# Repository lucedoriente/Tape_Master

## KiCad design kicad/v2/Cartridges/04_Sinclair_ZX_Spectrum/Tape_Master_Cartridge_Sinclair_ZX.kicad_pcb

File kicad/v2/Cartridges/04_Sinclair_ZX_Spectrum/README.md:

# Tape Master v2 — Cartuccia #04: Sinclair ZX Spectrum / ZX81 / Timex Sinclair

Modulo di interfaccia cassetta hardware conforme allo standard **Tape Master v2 (Tape/Cassette Master Exerciser & Signal Digitizer)** progettato da **Alessio Iodice**.

---

## 1. Modelli e Piattaforme Supportate
La cartuccia supporta la totalità della famiglia Sinclair a 8 bit e i relativi cloni compatibili:
- **Sinclair ZX80 / ZX81** (jack standard 3.5 mm MIC/EAR)
- **Sinclair ZX Spectrum 16K / 48K** ("Rubber Keys" e "Plus")
- **Sinclair ZX Spectrum 128K** ("Toastrack")
- **Sinclair ZX Spectrum +2** (Grigio con Datacorder integrato e prese ausiliarie)
- **Sinclair ZX Spectrum +2A / +2B / +3** (Nero - Amstrad design)
- **Timex Sinclair 1000 / 1500 / 2068**
- **Cloni internazionali**: Microdigital TK85, TK90X, TK95 (Brasile), Didaktik Gama / M (Cecoslovacchia), Pentagon / Scorpion (URSS).

---

## 2. Architettura Elettronica e Circuiti di Segnale

### A. Uscita Verso il Computer (`SPECTRUM_EAR` / Jack J2)
- **Livello Segnale e Attenuazione**: Il microcontrollore Tape Master genera segnali digitali a 3.3V/5V (`TAPE_EMU_OUT`). La porta EAR dello Spectrum accetta ampiezze nominali da $0.7\text{ V}$ a $1.5\text{ V}_\text{pp}$.
- **Buffer di Pilotaggio**: Buffer invertitore open-collector ad alta velocità **74HCT06** (`U2`), configurato a doppio stadio con resistenze di pull-up da $4.7\text{ k}\Omega$ (`R8`, `R9`) a +5V.
- **Partitore e Disaccoppiamento AC**: Partitore resistivo simmetrico $1\text{ k}\Omega / 1\text{ k}\Omega$ (`R6`, `R7`) per ridurre il segnale a circa $1.25\text{ V}_\text{pp}$, seguito da condensatore elettrolitico/tantalio SMD da $4.7\ \mu\text{F}$ (`C4`) per il disaccoppiamento della componente continua.

### B. Ingresso dal Computer (`SPECTRUM_MIC` / Jack J3)
- **Doppio Percorso di Acquisizione**:
  1. **Percorso Digitale MCU (`TAPE_REC_IN`)**: Partitore resistivo $2.2\text{ k}\Omega / 3.3\text{ k}\Omega$ (`R1`, `R2`) con stadio di clamp a diodi Schottky ultraveloci **BAT54S** (`D1`) verso GND e +3.3V, per una cattura a squadratura perfetta senza jitter.
  2. **Percorso Analogico Digitizer (`AUDIO_RAW_L`)**: Disaccoppiamento in frequenza tramite condensatore da $4.7\ \mu\text{F}$ (`C5`) diretto al convertitore analogico ADC e alla barra VU-meter a 10 segmenti frontale.

### C. Controllo Motore Remoto (`SPECTRUM_REM_A` / Header J4)
- Interruttore a stato solido basato su MOSFET a canale N **2N7002** (`Q1`) pilotato dalla linea `MOTOR_SENSE` con resistenza di pull-up da $10\text{ k}\Omega$ (`R3`), in grado di emulare il relè del telecomando registratore per registratori esterni compatibili.

### D. Protezione ESD e Auto-Riconoscimento Smart Plug&Play
- **Protezione TVS**: Array di diodi ad altissima velocità **USBLC6-2SC6** (`D2`) su tutte le linee esterne esposte (`EAR`, `MIC`, `REM_A`).
- **EEPROM I2C 24C02 (`U1`)**: Indirizzo hardware `0x54` (`A2=1`, `A1=0`, `A0=0`), contenente il descrittore binario Plug&Play con identificativo cartuccia `#04`, mapping piedini e parametri di temporizzazione ULA.

---

## 3. Connettività Esterna e Banco di Collaudo

### Connettori Audio Jack 3.5 mm TRS (CUI SJ1-3533NG)
- **`J2` (`EAR` / Riproduzione verso Spectrum)**:
  - `Tip (T)`: Segnale `SPECTRUM_EAR`
  - `Ring (R)`: Connesso a Tip per piena compatibilità con cavetti sia mono sia stereo
  - `Sleeve (S)`: Massa (`GND`)
- **`J3` (`MIC` / Registrazione dallo Spectrum)**:
  - `Tip (T)`: Segnale `SPECTRUM_MIC`
  - `Ring (R)`: Connesso a Tip per compatibilità con cavetti mono e stereo
  - `Sleeve (S)`: Massa (`GND`)

### Pin Header Banco di Prova (`J4` - Maschio 1x06 passo 2.54 mm)
| Pin | Segnale Serigrafato | Funzione Elettrica |
| :---: | :---: | :--- |
| **1** | `GND` | Riferimento di massa 0V |
| **2** | `+5V` | Alimentazione secondaria ausiliaria |
| **3** | `EAR` | Linea audio riproduzione diretta / oscilloscopio |
| **4** | `MIC` | Linea audio acquisizione grezza / analizzatore |
| **5** | `REM` | Linea controllo motore registratore |
| **6** | `GND` | Riferimento di massa 0V |

---

## 4. Specifiche Meccaniche e PCB
- **Dimensioni Esterne**: $74.00\text{ mm} \times 55.00\text{ mm}$ con profilo Edge.Cuts standard.
- **Intagli Laterali di Ritenuta**: Due aperture $6.00\text{ mm} \times 8.00\text{ mm}$ per le leve di aggancio rapido (latch) del connettore Mainboard.
- **Connettore Bus**: $2 \times 20$ contatti femmina a 90° (`J1`), perfettamente complanare alla Mainboard.
- **Finitura**: Piani di massa rame continui su Top (`F.Cu`) e Bottom (`B.Cu`), serigrafia con dicitura d'autore `© 2026 by Alessio Iodice`.

---

## 5. Validazione KiCad 9.0 e File di Fabbricazione
- **Controllo Regole Elettriche (ERC)**: `0 errori / 0 avvisi`
- **Controllo Regole di Design (DRC)**: `0 violazioni / 0 net non connesse / 0 discrepanze netlist-PCB`
- **File Inclusi**:
  - `Tape_Master_Cartridge_Sinclair_ZX.kicad_sch` (Schema elettrico)
  - `Tape_Master_Cartridge_Sinclair_ZX.kicad_pcb` (Layout sbrogliato e verificato)
  - `Tape_Master_Cartridge_Sinclair_ZX.pdf` (Tavola vettoriale dello schema)
  - `Tape_Master_Cartridge_Sinclair_ZX.step` (Modello 3D solido MCAD con tutti i componenti integrati)
  - `Tape_Master_Cartridge_Sinclair_ZX_Top.pdf` / `Bottom.pdf` / `Top.svg` (Plottaggi serigrafia e rame)
  - `gerbers/` (26 file standard RS-274X e forature Excellon pronti per JLCPCB/PCBWay).

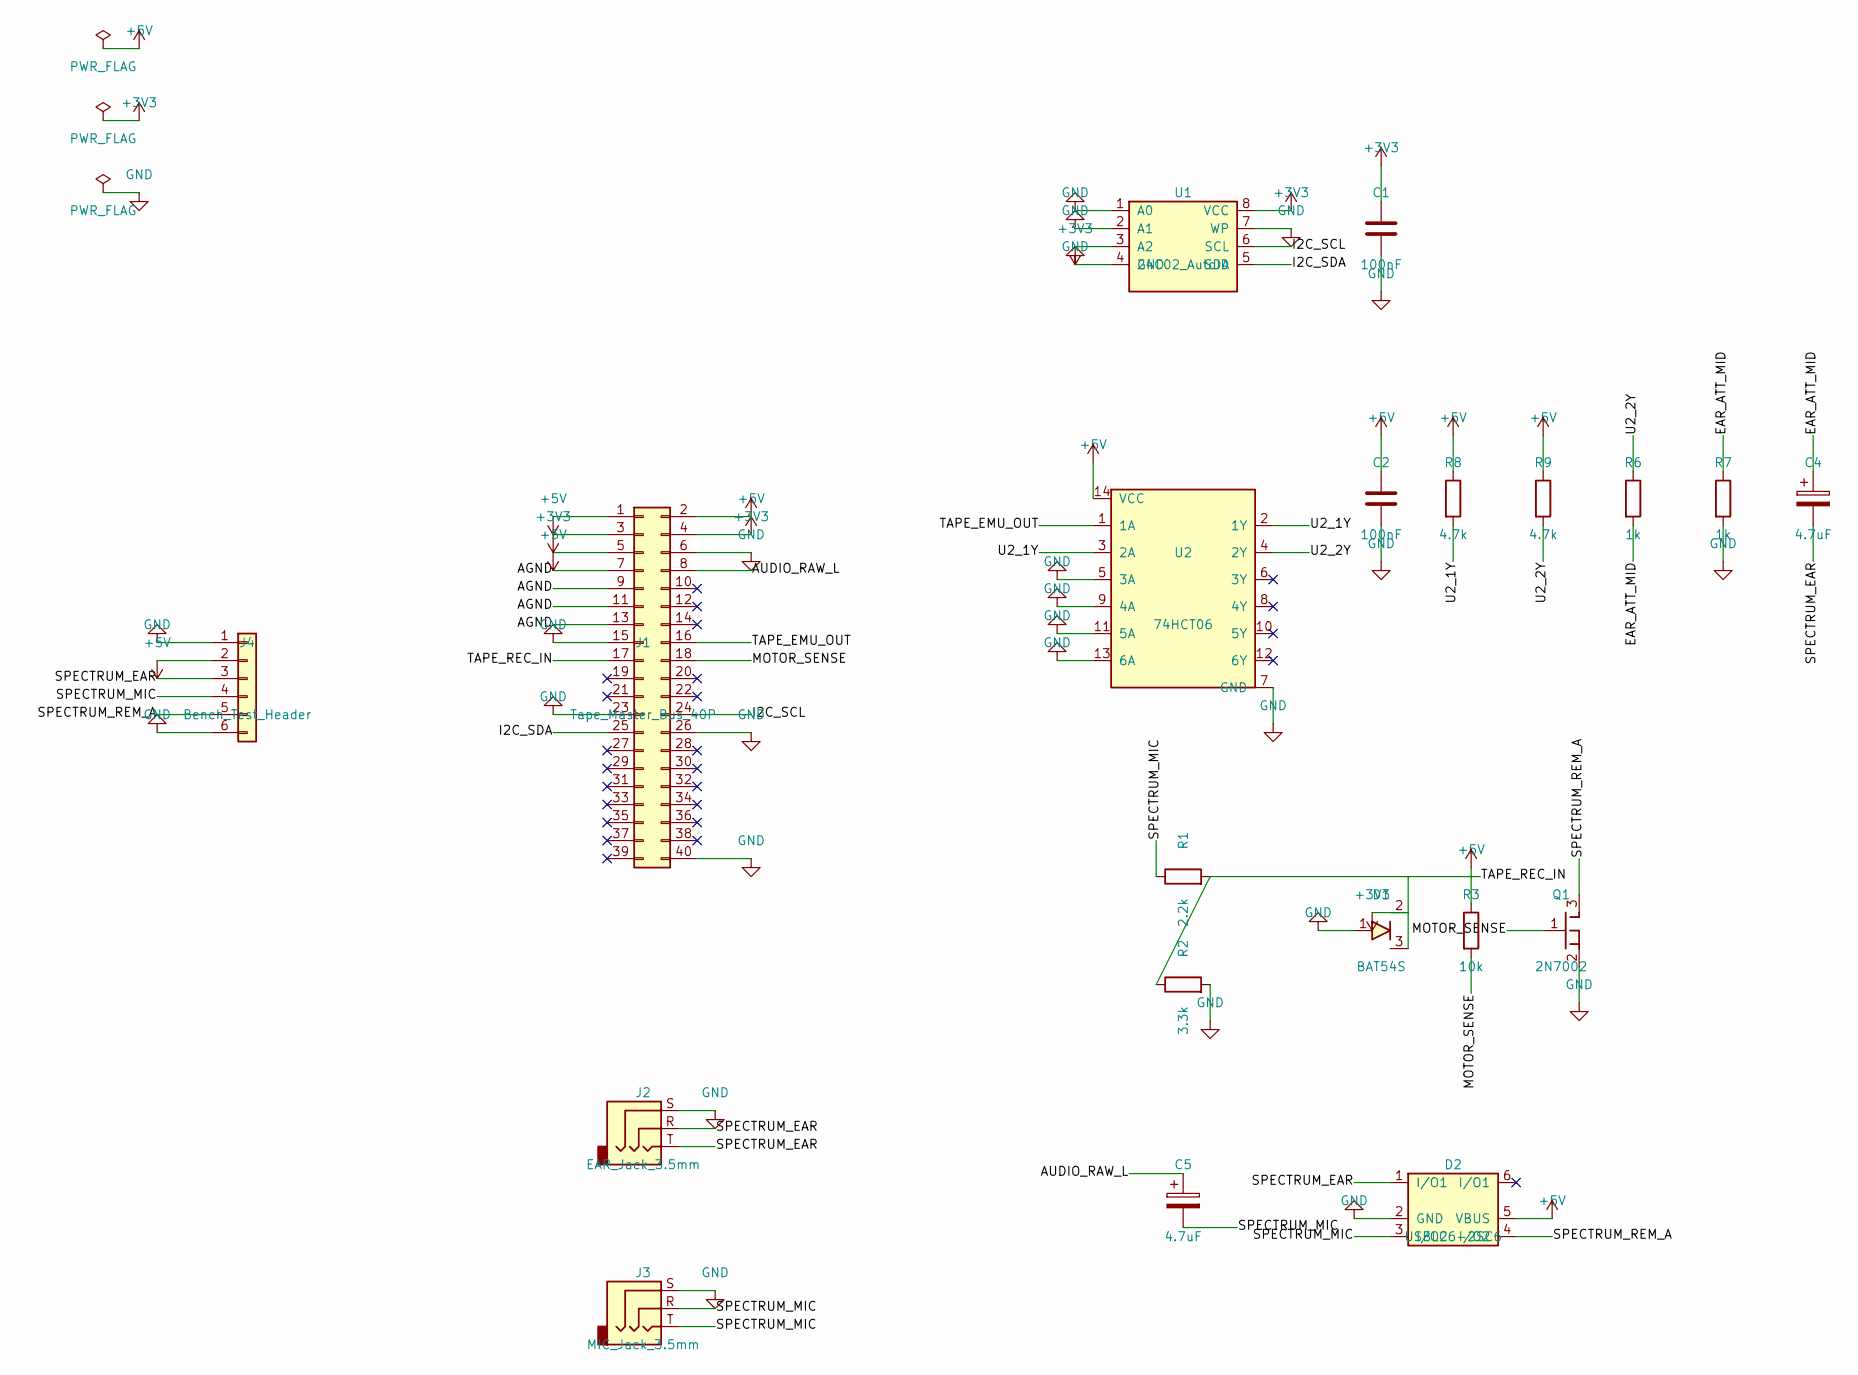
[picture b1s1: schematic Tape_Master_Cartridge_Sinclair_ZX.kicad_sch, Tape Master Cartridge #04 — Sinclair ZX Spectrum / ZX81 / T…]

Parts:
C1, C2: 100nF; C_0805_2012Metric
C4, C5: 4.7uF; CP_Elec_5x5.4
D1: BAT54S; SOT-23
D2: USBLC6-2SC6; SOT-23-6
J1: Tape_Master_Bus_40P; PinSocket_2x20_P2.54mm_Horizontal_Cartridge
J2: EAR_Jack_3.5mm; Jack_3.5mm_CUI_SJ1-3525N_Horizontal
J3: MIC_Jack_3.5mm; Jack_3.5mm_CUI_SJ1-3525N_Horizontal
J4: Bench_Test_Header; PinHeader_1x06_P2.54mm_Vertical
Q1: 2N7002; SOT-23
R1: 2.2k; R_0805_2012Metric
R2: 3.3k; R_0805_2012Metric
R3: 10k; R_0805_2012Metric
R6, R7: 1k; R_0805_2012Metric
R8, R9: 4.7k; R_0805_2012Metric
U1: 24C02_AutoID; SOIC-8_3.9x4.9mm_P1.27mm
U2: 74HCT06; SOIC-14_3.9x8.7mm_P1.27mm

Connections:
+3V3: C1.1, D1.2 (C2), J1.3, J1.4, U1.3 (A2), U1.8 (VCC)
+5V: C2.1, D2.5 (VBUS), J1.1, J1.2, J1.5, J4.2, R3.1, R8.1, R9.1, U2.14 (VCC)
/AGND: J1.7, J1.9, J1.11, J1.13
/AUDIO_RAW_L: C5.1, J1.8
/EAR_ATT_MID: C4.1, R6.2, R7.1
/I2C_SCL: J1.24, U1.6 (SCL)
/I2C_SDA: J1.25, U1.5 (SDA)
/MOTOR_SENSE: J1.18, Q1.1 (G), R3.2
/SPECTRUM_EAR: C4.2, D2.1 (I/O1), J2.R, J2.T, J4.3
/SPECTRUM_MIC: C5.2, D2.3 (I/O2), J3.R, J3.T, J4.4, R1.1
/SPECTRUM_REM_A: D2.4 (I/O2), J4.5, Q1.3 (D)
/TAPE_EMU_OUT: J1.16, U2.1 (1A)
/TAPE_REC_IN: D1.3 (C1A2), J1.17, R1.2, R2.1
/U2_1Y: R8.2, U2.2 (1Y), U2.3 (2A)
/U2_2Y: R6.1, R9.2, U2.4 (2Y)
GND: C1.2, C2.2, D1.1 (A1), D2.2 (GND), J1.6, J1.15, J1.23, J1.26, J1.40, J2.S, J3.S, J4.1, J4.6, Q1.2 (S), R2.2, R7.2, U1.1 (A0), U1.2 (A1), U1.4 (GND), U1.7 (WP), U2.5 (3A), U2.7 (GND), U2.9 (4A), U2.11 (5A), U2.13 (6A)

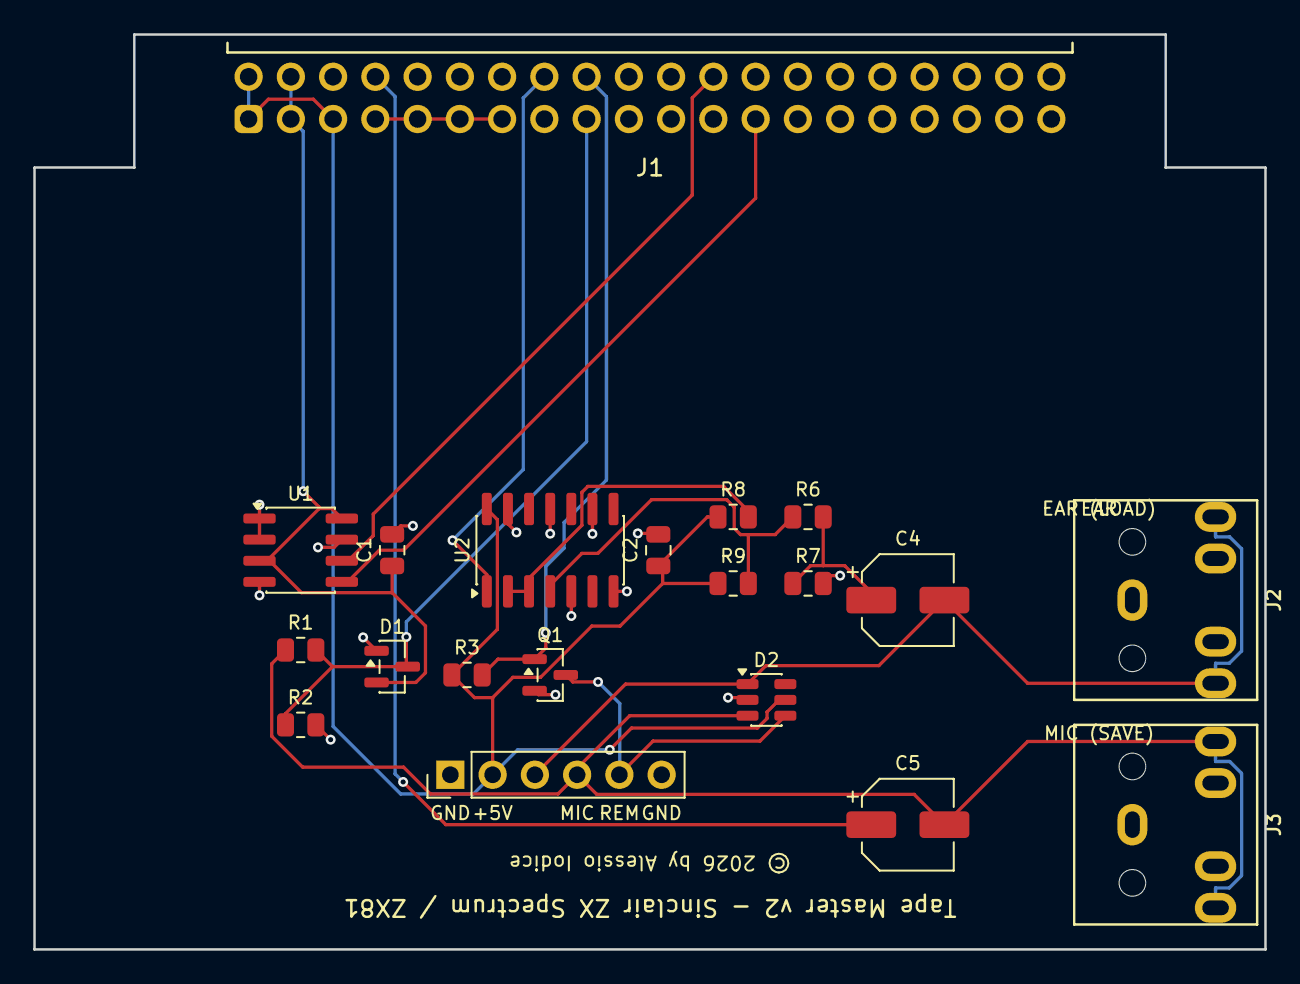
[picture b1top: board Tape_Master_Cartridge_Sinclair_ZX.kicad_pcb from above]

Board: 2 copper layers, 74.0 x 55.0 mm, 20 parts (0 on the bottom side), 16 nets.

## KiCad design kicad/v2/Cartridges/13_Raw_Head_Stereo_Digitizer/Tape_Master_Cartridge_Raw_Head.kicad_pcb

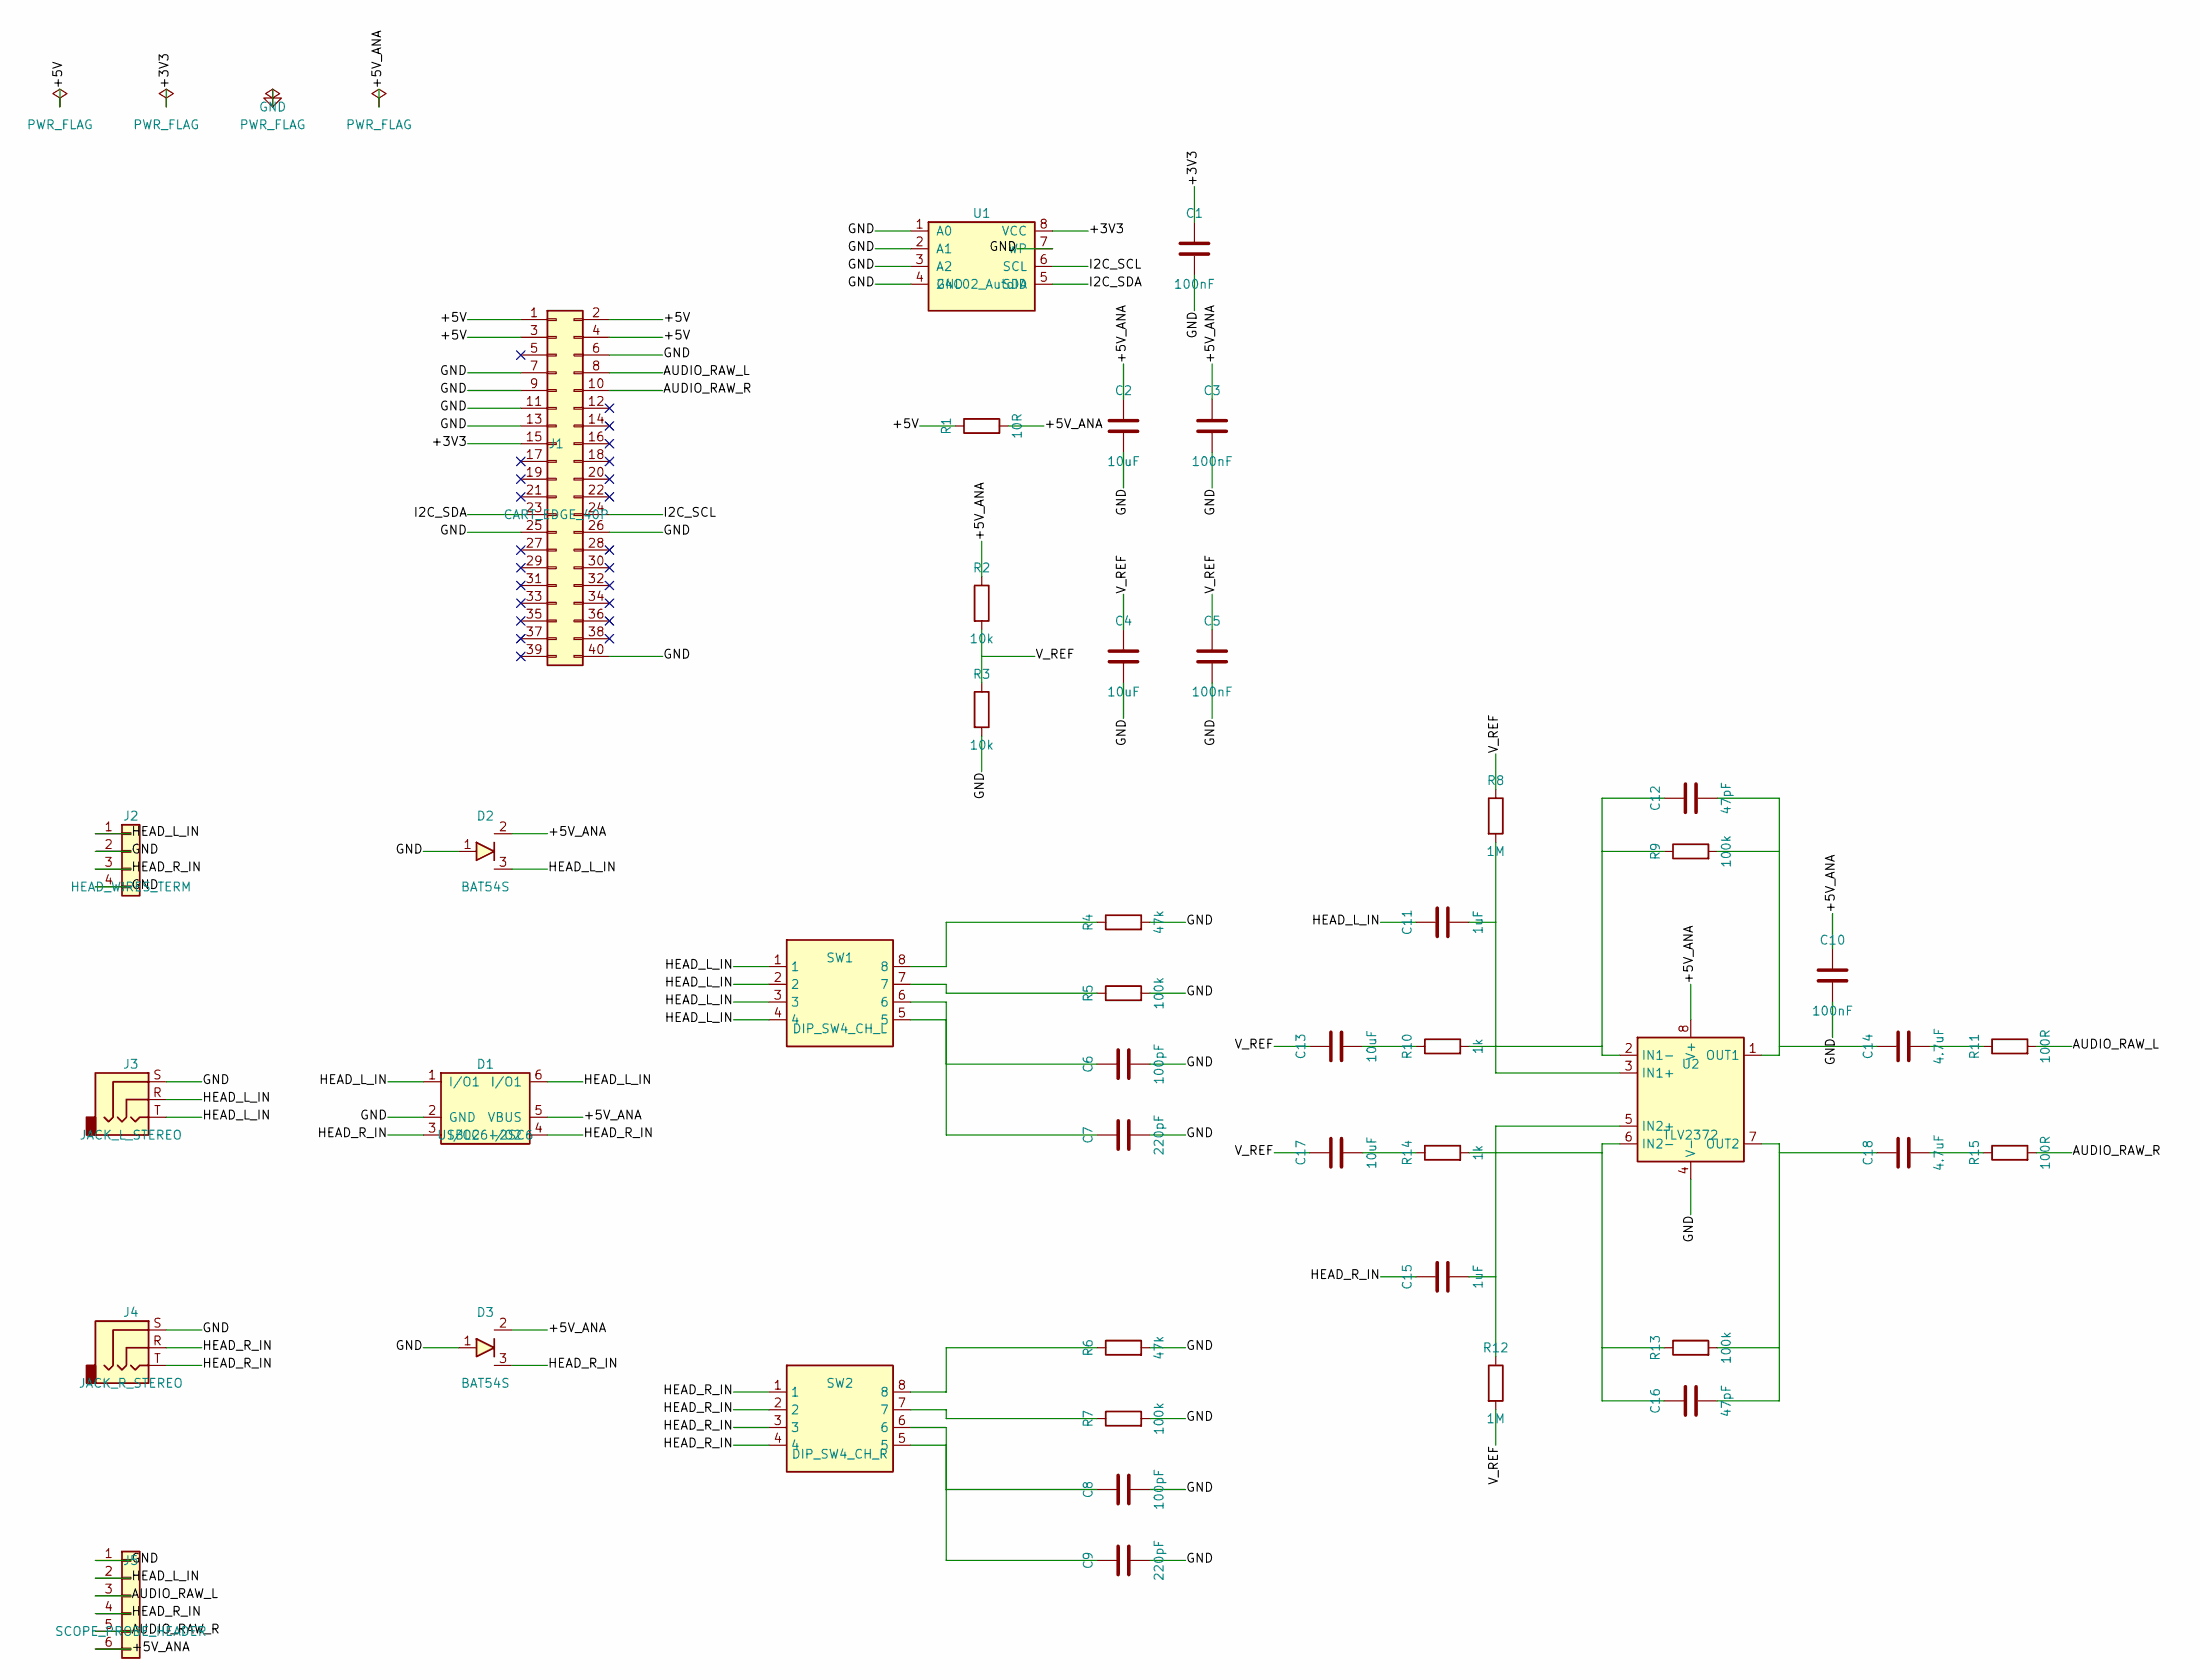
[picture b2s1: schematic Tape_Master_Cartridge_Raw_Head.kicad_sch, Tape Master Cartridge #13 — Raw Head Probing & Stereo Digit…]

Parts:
C1, C3, C5, C10: 100nF; C_0805_2012Metric
C2, C4, C13, C17: 10uF; C_0805_2012Metric
C6, C8: 100pF; C_0805_2012Metric
C7, C9: 220pF; C_0805_2012Metric
C11, C15: 1uF; C_0805_2012Metric
C12, C16: 47pF; C_0805_2012Metric
C14, C18: 4.7uF; C_0805_2012Metric
D1: USBLC6-2SC6; SOT-23-6
D2, D3: BAT54S; SOT-23
J1: CART_EDGE_40P; PinSocket_2x20_P2.54mm_Horizontal_Cartridge
J2: HEAD_WIRES_TERM; TerminalBlock_Phoenix_MPT-0,5-4-2.54_1x04_P2.54mm_Horizontal
J3: JACK_L_STEREO; Jack_3.5mm_CUI_SJ-3523-SMT_Horizontal
J4: JACK_R_STEREO; Jack_3.5mm_CUI_SJ-3523-SMT_Horizontal
J5: SCOPE_PROBE_HEADER; PinHeader_1x06_P2.54mm_Vertical
R1: 10R; R_0805_2012Metric
R2, R3: 10k; R_0805_2012Metric
R4, R6: 47k; R_0805_2012Metric
R5, R7, R9, R13: 100k; R_0805_2012Metric
R8, R12: 1M; R_0805_2012Metric
R10, R14: 1k; R_0805_2012Metric
R11, R15: 100R; R_0805_2012Metric
SW1: DIP_SW4_CH_L; SW_DIP_SPSTx04_Slide_6.7x11.72mm_W8.61mm_P2.54mm_LowProfile
SW2: DIP_SW4_CH_R; SW_DIP_SPSTx04_Slide_6.7x11.72mm_W8.61mm_P2.54mm_LowProfile
U1: 24C02_AutoID; SOIC-8_3.9x4.9mm_P1.27mm
U2: TLV2372; SOIC-8_3.9x4.9mm_P1.27mm

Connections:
/+3V3: C1.1, J1.15, U1.8 (VCC)
/+5V: J1.1, J1.2, J1.3, J1.4, R1.1
/+5V_ANA: C2.1, C3.1, C10.1, D1.5 (VBUS), D2.2 (C2), D3.2 (C2), J5.6, R1.2, R2.1, U2.8 (V+)
/AUDIO_RAW_L: J1.8, J5.3, R11.2
/AUDIO_RAW_R: J1.10, J5.5, R15.2
/HEAD_L_IN: C11.1, D1.1 (I/O1), D1.6 (I/O1), D2.3 (C1A2), J2.1, J3.R, J3.T, J5.2, SW1.1, SW1.2, SW1.3, SW1.4
/HEAD_R_IN: C15.1, D1.3 (I/O2), D1.4 (I/O2), D3.3 (C1A2), J2.3, J4.R, J4.T, J5.4, SW2.1, SW2.2, SW2.3, SW2.4
/I2C_SCL: J1.24, U1.6 (SCL)
/I2C_SDA: J1.23, U1.5 (SDA)
/V_REF: C4.1, C5.1, C13.1, C17.1, R2.2, R3.1, R8.1, R12.2
GND: C1.2, C2.2, C3.2, C4.2, C5.2, C6.2, C7.2, C8.2, C9.2, C10.2, D1.2 (GND), D2.1 (A1), D3.1 (A1), J1.6, J1.7, J1.9, J1.11, J1.13, J1.25, J1.26, J1.40, J2.2, J2.4, J3.S, J4.S, J5.1, R3.2, R4.2, R5.2, R6.2, R7.2, U1.1 (A0), U1.2 (A1), U1.3 (A2), U1.4 (GND), U1.7 (WP), U2.4 (V-)
unnamed: C6.1, SW1.6
unnamed: C7.1, SW1.5
unnamed: C8.1, SW2.6
unnamed: C9.1, SW2.5
unnamed: C13.2, R10.1
unnamed: C14.2, R11.1
unnamed: C17.2, R14.1
unnamed: C18.2, R15.1
unnamed: R4.1, SW1.8
unnamed: R5.1, SW1.7
unnamed: R6.1, SW2.8
unnamed: R7.1, SW2.7
unnamed: C11.2, R8.2, U2.3 (IN1+)
unnamed: C12.1, R9.1, R10.2, U2.2 (IN1-)
unnamed: C15.2, R12.1, U2.5 (IN2+)
unnamed: C16.1, R13.1, R14.2, U2.6 (IN2-)
unnamed: C12.2, C14.1, R9.2, U2.1 (OUT1)
unnamed: C16.2, C18.1, R13.2, U2.7 (OUT2)

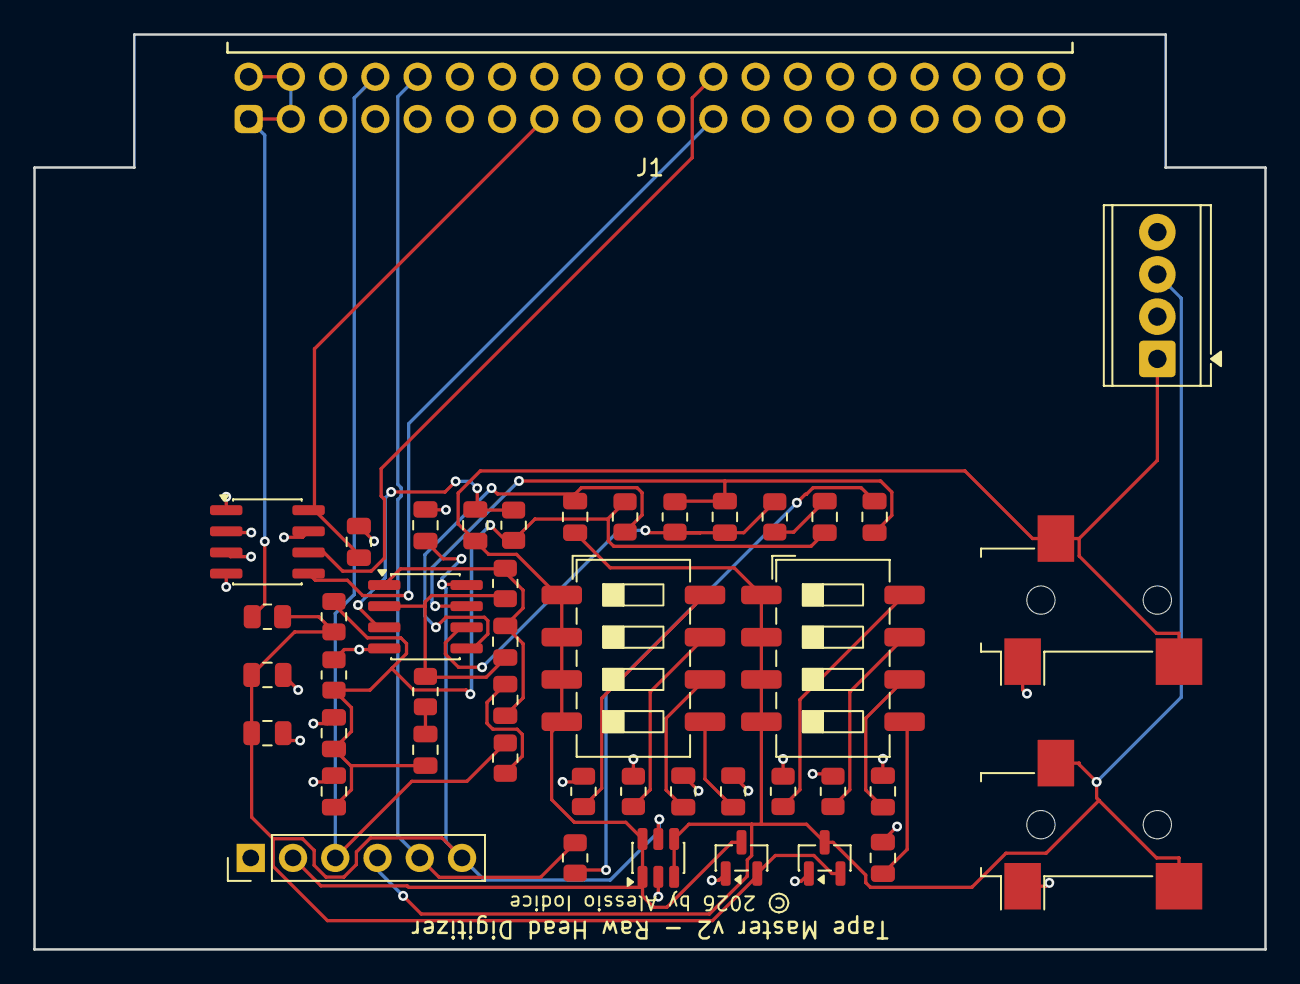
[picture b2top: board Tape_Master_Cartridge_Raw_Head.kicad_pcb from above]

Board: 2 copper layers, 74.0 x 55.0 mm, 45 parts (0 on the bottom side), 29 nets.

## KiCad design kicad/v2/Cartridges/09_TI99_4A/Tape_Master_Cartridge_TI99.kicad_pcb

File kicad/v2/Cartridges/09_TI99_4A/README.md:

# Tape Master v2 — Cartuccia 09: Texas Instruments TI-99/4A Tape Interface

| Proprietà | Dettaglio / Valore |
| :--- | :--- |
| **Progetto** | Tape Master Exerciser & Signal Digitizer v2 |
| **Modulo** | Cartuccia Espansione #09 — Texas Instruments TI-99/4A (`09_TI99_4A`) |
| **Piattaforme Compatibili** | Texas Instruments TI-99/4 e TI-99/4A (microprocessore a 16 bit TMS9900 @ 3.0 MHz) |
| **Periferiche Supportate** | Registratore a nastro dedicato TI Program Recorder PHP2700, registratori audio standard tramite cavo PHA2000 o cavo seriale maschio/femmina DE-9 dritto |
| **Autore & Hardware Designer** | Alessio Iodice (`alessio67@gmail.com`) |
| **Data di Rilascio** | 2026-11-06 |
| **Revisione** | 2.0 (KiCad 9.0 Nativo) |
| **Licenza** | CC BY-NC-SA 4.0 |
| **Stato Validazione KiCad 9** | **0 Violazioni ERC / 0 Violazioni DRC / 0 Net Non Connesse / 0 Parity Issues** |

---

## 1. Descrizione Architetturale

La **Cartuccia 09: Texas Instruments TI-99/4A** interfaccia il sistema **Tape Master v2** alla porta a nastro a 9 poli posta sul retro della console TI-99/4 e TI-99/4A, adottando il connettore standard **D-Sub 9-pin Femmina (DE-9 Socket)** a montaggio su circuito stampato ([DSUB-9_Socket_Horizontal_P2.77x2.84mm_EdgePinOffset9.40mm](file:///C:/Users/aless/OneDrive/temp/Manutenzione/Kicad_Project/Tape_Master/kicad/v2/Cartridges/09_TI99_4A/Tape_Master_Cartridge_TI99.kicad_pcb)).

L'architettura cassetta del TI-99/4A è unica nel panorama degli home computer degli anni '80:
- È controllata direttamente dal chip **TMS9901 PSI** tramite registri **CRU (Communications Register Unit)**;
- Integra **fotoaccoppiatori e stadi di isolamento ottico** interni alla console;
- Supporta nativamente **due registratori simultanei**: **Cassette 1 (CS1)** dedicato alla lettura, e **Cassette 2 (CS2)** per lettura e scrittura;
- Utilizza modulazione audio FSK a 1200 baud nominali ($1379\text{ Hz}$ per il bit `1` / Mark, $689\text{ Hz}$ per il bit `0` / Space).

### Caratteristiche Elettriche Chiave
1. **Canale Riproduzione Dati (TAPE_IN - Pin 8 DE-9)**:
   - Ingresso audio FSK del computer TI-99/4A (comune per la lettura da CS1 o CS2, associato a CRU Bit 27).
   - Pilotaggio tramite buffer open-collector ad alta velocità **74HCT06** (`U2`) configurato a doppio stadio logico con resistori di pull-up da $4.7\text{ k}\Omega$ (`R7`, `R8`) a `+5V`.
   - Rete passiva di disaccoppiamento AC e calibrazione dinamica: resistore serie $1\text{ k}\Omega$ (`R9`), condensatore di disaccoppiamento da $4.7\ \mu\text{F}$ (`C3`) e resistore di carico shunt da $10\text{ k}\Omega$ (`R10`) verso massa, garantendo un'onda audio calibrata e pulita per il comparatore operazionale interno della console.
2. **Canale Registrazione Dati (CS2_OUT - Pin 3 DE-9)**:
   - Uscita audio FSK dal computer TI-99/4A durante le operazioni di salvataggio (`SAVE "CS2"` o `OLD "CS2"`, CRU Bit 25).
   - Traslazione rapida di livello logico verso i 3.3V tramite partitore resistivo ($R_1 = 2.2\text{ k}\Omega$, $R_2 = 3.3\text{ k}\Omega$) protetto da clamp a doppio diodo Schottky ultra-veloce **BAT54S** (`D1`) verso `+3.3V` e `GND`, collegato alla linea `TAPE_REC_IN` dell'RP2040.
   - Derivazione audio analogica AC con condensatore di blocco DC da $4.7\ \mu\text{F}$ (`C4`), filtro RC passa-basso anti-aliasing ($R_{11} = 1\text{ k}\Omega$, $C_5 = 10\text{ nF}$) e shunt da $10\text{ k}\Omega$ (`R12`) collegata al canale ADC `AUDIO_RAW_L` per il pilotaggio dinamico del display OLED e del VU-meter a 10 segmenti del front panel.
3. **Gestione Indipendente del Doppio Motore (CS1 e CS2)**:
   - **Registratore 1 (`TI_CS1_MOTOR_P`, Pin 1 DE-9 - CRU Bit 22)**:
     - Resistore di pull-up da $10\text{ k}\Omega$ (`R3`) a `+5V`.
     - Partitore $2.2\text{ k}\Omega / 3.3\text{ k}\Omega$ (`R4`, `R5`) con clamp Schottky **BAT54S** (`D2`) attestato sulla linea `MOTOR_SENSE` del bus universale. Quando il computer attiva il motore di CS1, il contatto dell'optoisolatore interno alla console chiude Pin 1 a massa, portando `MOTOR_SENSE` a 0V (attivo basso).
     - N-MOSFET di commutazione **2N7002** (`Q1`) pilotato dalla linea `MOTOR_CTRL` (con resistore serie di gate `R13` da $100\ \Omega$ e pull-down `R14` da $100\text{ k}\Omega$) per consentire al Tape Master di azionare direttamente il motore di un registratore esterno a banco.
   - **Registratore 2 (`TI_CS2_MOTOR_P`, Pin 6 DE-9 - CRU Bit 23)**:
     - Resistore di pull-up da $10\text{ k}\Omega$ (`R15`) a `+5V`.
     - Partitore $2.2\text{ k}\Omega / 3.3\text{ k}\Omega$ (`R16`, `R17`) con clamp Schottky **BAT54S** (`D4`) attestato sulla linea ausiliaria configurabile **`AUX_GPIO1`** (Pin 21 del bus a 40 pin), consentendo al firmware del Tape Master di monitorare separatamente e in tempo reale lo stato del secondo registratore.
4. **Campionamento Audio Gate (`TI_AUDIO_GATE` - Pin 4 DE-9 - CRU Bit 24)**:
   - Partitore resistivo ($R_{18} = 2.2\text{ k}\Omega$, $R_{19} = 3.3\text{ k}\Omega$) con clamp Schottky **BAT54S** (`D5`) collegato alla linea **`AUX_GPIO2`** (Pin 22 del bus a 40 pin) per rilevare l'abilitazione hardware del segnale audio operata dalla console.
5. **Protezione ESD / Transitori**:
   - Due array integrati a diodi TVS ultra-rapidi a bassissima capacità **USBLC6-2SC6** (`U3` e `U4`, package SOT-23-6L) proteggono le linee esterne del connettore DE-9 da scariche elettrostatiche fino a $\pm 15\text{ kV}$.
6. **Smart Plug & Play (Auto-ID Cartridge)**:
   - EEPROM I2C seriale **24C02** (`U1`) all'indirizzo `0x50` con descrittore hardware binario univoco TI-99/4A.
   - Pin 26 del bus principale `CART_DETECT_N` vincolato permanentemente a massa per rilevamento hardware istantaneo all'inserimento.

---

## 2. Centralizzazione Diagnostica sul Front Panel (Daughterboard)

Come prescritto dalle regole ufficiali di progetto `tape-master-rules.md`, tutti i LED diagnostici sono centralizzati sul pannello frontale (`Tape_Master_UI_Panel`), evitando duplicati non visibili a banco sulla cartuccia.

I 5 LED diagnostici standardizzati sul pannello operatore riflettono il funzionamento della cartuccia TI-99/4A:

| Riferimento UI | Colore | Serigrafia Standard | Segnale Mappato per TI-99/4A | Funzione Operativa |
| :---: | :---: | :---: | :--- | :--- |
| **D2** | Verde | **`PLAY`** | `TI_TAPE_IN` (Pin 8 DE-9) | Trasmissione dati FSK verso la console TI-99 (emulazione nastro / riproduzione file WAV o dump) |
| **D3** | Rosso | **`REC`** | `TI_CS2_OUT` (Pin 3 DE-9) | Ricezione dati FSK dalla console TI-99/4A verso il Tape Master (salvataggio dump da `SAVE "CS2"`) |
| **D4** | Giallo | **`MOTOR`** | `TI_CS1_MOTOR_P` (Pin 1 DE-9) | Relè motore CS1 chiuso dalla console o forzatura motore esterna attiva |
| **D5** | Blu | **`SIGNAL`** | Rilevamento portante FSK | Rilevamento toni FSK a $1379\text{ Hz}$ (Mark) o $689\text{ Hz}$ (Space) |
| **D6** | Verde | **`PWR`** | Alimentazione Tape Master | Alimentazione principale di sistema attiva (+5V / +3.3V) e MCU operativo |
| **D10..D19** | 8V/1G/1R | **`AZIMUTH / VU-METER`** | Livello picco ADC `AUDIO_RAW_L` | Barra VU-meter per regolazione azimut / intensità segnale audio analogico in ingresso |

---

## 3. Doppia Connettività Esterna

La cartuccia adotta l'architettura a **doppia porta**:
1. **`J2` — Presa D-Sub 9-Pin Femmina (DE-9 Socket)**: Connettore orizzontale a montaggio su circuito stampato conforme al pinout originale TI-99/4A. Permette il collegamento diretto alla console tramite cavo seriale dritto standard 1:1 maschio-femmina.
2. **`J3` — Pin-Header Maschio Breakout 1x09 passo 2.54 mm**: Pin-header orizzontale serigrafato posto sul bordo inferiore del PCB, progettato per collegamenti rapidi a banco, oscilloscopio, analizzatore di stati logici e cavi volanti.

### Piedinatura Connettori (`J2` e `J3`)

| Pin # J3 | Pin # J2 (DE-9) | Serigrafia J3 | Segnale | Direzione Elettrica | Descrizione Tecnica TI-99 |
| :---: | :---: | :--- | :--- | :---: | :--- |
| **1** | **2, 5, 7, 9** | `GND` | `GND` | Riferimento | Massa comune di segnale e ritorno schermo |
| **2** | — | `+5V` | `+5V` | Potenza | Tensione alimentazione Tape Master per test a banco |
| **3** | **1** | `M1` | `TI_CS1_MOTOR_P` | Dalla console (Output) | Comando motore registratore 1 (CS1, CRU Bit 22) |
| **4** | **3** | `OUT` | `TI_CS2_OUT` | Dalla console (Output) | Uscita audio FSK da console a registratore 2 (MIC, CRU Bit 25) |
| **5** | **4** | `GATE` | `TI_AUDIO_GATE` | Dalla console (Output) | Segnale di abilitazione e gating audio (CRU Bit 24) |
| **6** | **6** | `M2` | `TI_CS2_MOTOR_P` | Dalla console (Output) | Comando motore registratore 2 (CS2, CRU Bit 23) |
| **7** | **8** | `IN` | `TI_TAPE_IN` | Verso console (Input) | Ingresso audio FSK al comparatore della console (EAR, CRU Bit 27) |
| **8** | **2, 5, 7, 9** | `GND` | `GND` | Riferimento | Ritorno di massa ausiliario |
| **9** | **2, 5, 7, 9** | `GND` | `GND` | Riferimento | Ritorno di massa ausiliario |

---

## 4. Specifiche Meccaniche e Bordo Scheda

- **Dimensioni**: $74.00\text{ mm} \times 55.00\text{ mm}$ conforme allo standard unificato delle Cartucce Tape Master v2.
- **Intagli Meccanici di Blocco**: Due intagli precisi su layer `Edge.Cuts` ($6.0\text{ mm} \times 8.0\text{ mm}$) per l'alloggiamento delle leve di ritenuta del connettore `J1` della Mainboard.
- **Complanarità**: Connettore maschio ad angolo retto sulla Mainboard e connettore femmina ad angolo retto sulla Cartuccia (`J1`) garantiscono una perfetta complanarità tra le due schede.
- **Serigrafia di Copyright**: Prescritta e presente su `F.Silkscreen` con la dicitura ufficiale `© 2026 by Alessio Iodice`.

---

## 5. File di Rilascio e Produzione

- Schema Elettrico KiCad: `Tape_Master_Cartridge_TI99.kicad_sch`
- Layout PCB KiCad: `Tape_Master_Cartridge_TI99.kicad_pcb`
- Modello 3D Meccanico Solido PCB Assemblato: `Tape_Master_Cartridge_TI99.step`
- Schema Elettrico Vettoriale: `Tape_Master_Cartridge_TI99.pdf` e `Tape_Master_Cartridge_TI99_Sch.svg`
- Disegno PCB Top Layer: `Tape_Master_Cartridge_TI99_Top.pdf` e `Tape_Master_Cartridge_TI99_Top.svg`
- Disegno PCB Bottom Layer: `Tape_Master_Cartridge_TI99_Bottom.pdf`
- Pacchetto Gerbers & Drills Produzione: cartella `gerbers/`
- Report di Validazione KiCad 9:
  - ERC: `Tape_Master_Cartridge_TI99-erc.rpt` (**0 errori / 0 warning**)
  - DRC: `Tape_Master_Cartridge_TI99-drc.rpt` (**0 violazioni / 0 unconnected / 0 parity**)

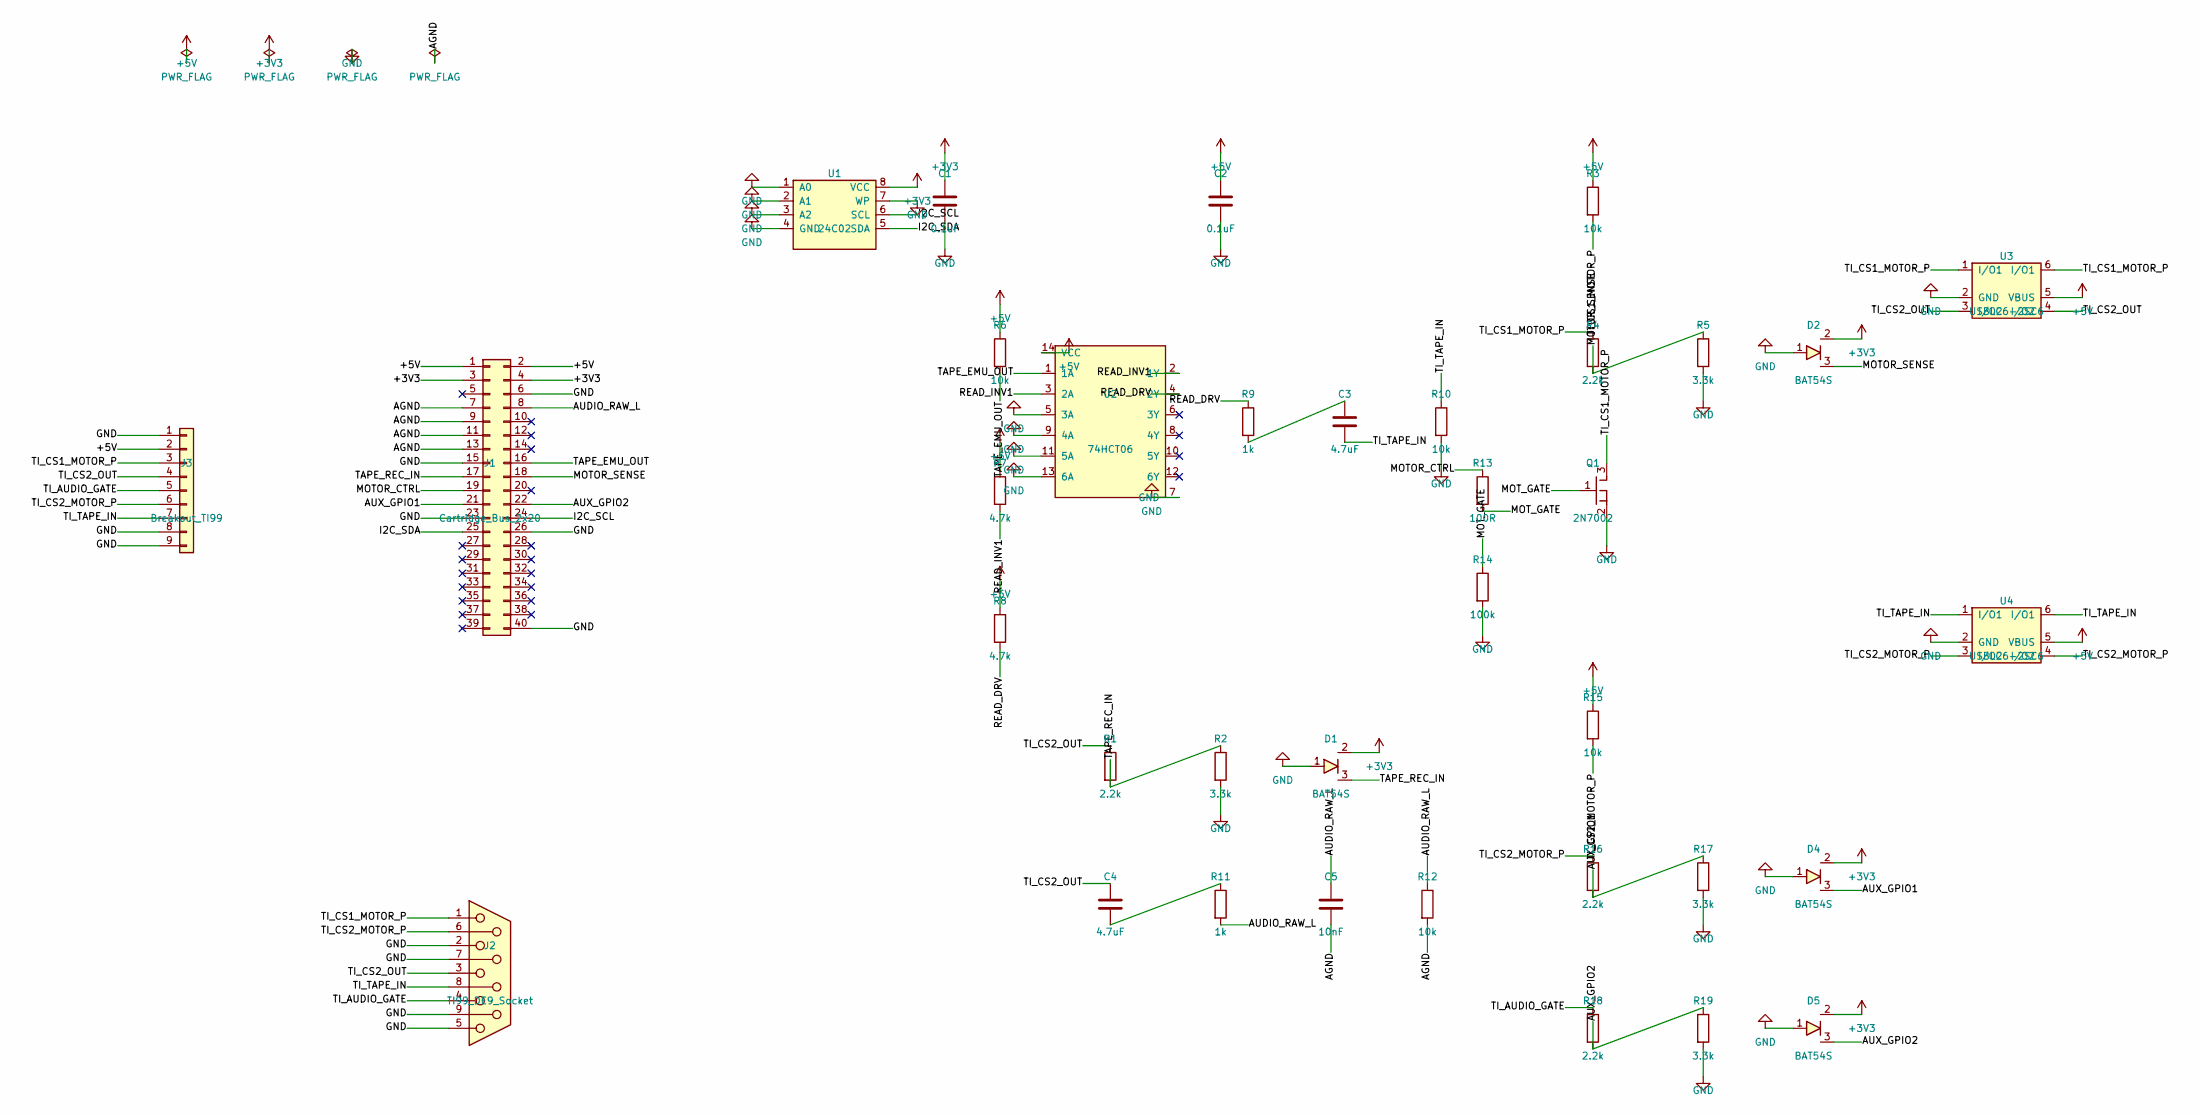
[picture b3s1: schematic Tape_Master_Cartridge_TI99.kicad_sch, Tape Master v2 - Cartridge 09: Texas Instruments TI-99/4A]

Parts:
C1, C2: 0.1uF; C_0805_2012Metric
C3, C4: 4.7uF; C_0805_2012Metric
C5: 10nF; C_0805_2012Metric
D1, D2, D4, D5: BAT54S; SOT-23
J1: Cartridge_Bus_2x20; PinSocket_2x20_P2.54mm_Horizontal_Cartridge
J2: TI99_DE9_Socket; DSUB-9_Socket_Horizontal_P2.77x2.84mm_EdgePinOffset9.40mm
J3: Breakout_TI99; PinHeader_1x09_P2.54mm_Vertical
Q1: 2N7002; SOT-23
R1, R4, R16, R18: 2.2k; R_0805_2012Metric
R2, R5, R17, R19: 3.3k; R_0805_2012Metric
R3, R6, R10, R12, R15: 10k; R_0805_2012Metric
R7, R8: 4.7k; R_0805_2012Metric
R9, R11: 1k; R_0805_2012Metric
R13: 100R; R_0805_2012Metric
R14: 100k; R_0805_2012Metric
U1: 24C02; SOIC-8_3.9x4.9mm_P1.27mm
U2: 74HCT06; SOIC-14_3.9x8.7mm_P1.27mm
U3, U4: USBLC6-2SC6; SOT-23-6

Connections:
+3V3: C1.1, D1.2 (C2), D2.2 (C2), D4.2 (C2), D5.2 (C2), J1.3, J1.4, U1.8 (VCC)
+5V: C2.1, J1.1, J1.2, J3.2, R3.1, R6.1, R7.1, R8.1, R15.1, U2.14 (VCC), U3.5 (VBUS), U4.5 (VBUS)
/AGND: C5.2, J1.7, J1.9, J1.11, J1.13, R12.2
/AUDIO_RAW_L: C5.1, J1.8, R11.2, R12.1
/AUX_GPIO1: D4.3 (C1A2), J1.21, R16.2, R17.1
/AUX_GPIO2: D5.3 (C1A2), J1.22, R18.2, R19.1
/I2C_SCL: J1.24, U1.6 (SCL)
/I2C_SDA: J1.25, U1.5 (SDA)
/MOTOR_CTRL: J1.19, R13.1
/MOTOR_SENSE: D2.3 (C1A2), J1.18, R4.2, R5.1
/MOT_GATE: Q1.1 (G), R13.2, R14.1
/READ_DRV: R8.2, R9.1, U2.4 (2Y)
/READ_INV1: R7.2, U2.2 (1Y), U2.3 (2A)
/TAPE_EMU_OUT: J1.16, R6.2, U2.1 (1A)
/TAPE_REC_IN: D1.3 (C1A2), J1.17, R1.2, R2.1
/TI_AUDIO_GATE: J2.4, J3.5, R18.1
/TI_CS1_MOTOR_P: J2.1, J3.3, Q1.3 (D), R3.2, R4.1, U3.1 (I/O1), U3.6 (I/O1)
/TI_CS2_MOTOR_P: J2.6, J3.6, R15.2, R16.1, U4.3 (I/O2), U4.4 (I/O2)
/TI_CS2_OUT: C4.1, J2.3, J3.4, R1.1, U3.3 (I/O2), U3.4 (I/O2)
/TI_TAPE_IN: C3.2, J2.8, J3.7, R10.1, U4.1 (I/O1), U4.6 (I/O1)
GND: C1.2, C2.2, D1.1 (A1), D2.1 (A1), D4.1 (A1), D5.1 (A1), J1.6, J1.15, J1.23, J1.26, J1.40, J2.2, J2.5, J2.7, J2.9, J3.1, J3.8, J3.9, Q1.2 (S), R2.2, R5.2, R10.2, R14.2, R17.2, R19.2, U1.1 (A0), U1.2 (A1), U1.3 (A2), U1.4 (GND), U1.7 (WP), U2.5 (3A), U2.7 (GND), U2.9 (4A), U2.11 (5A), U2.13 (6A), U3.2 (GND), U4.2 (GND)
unnamed: C3.1, R9.2
unnamed: C4.2, R11.1

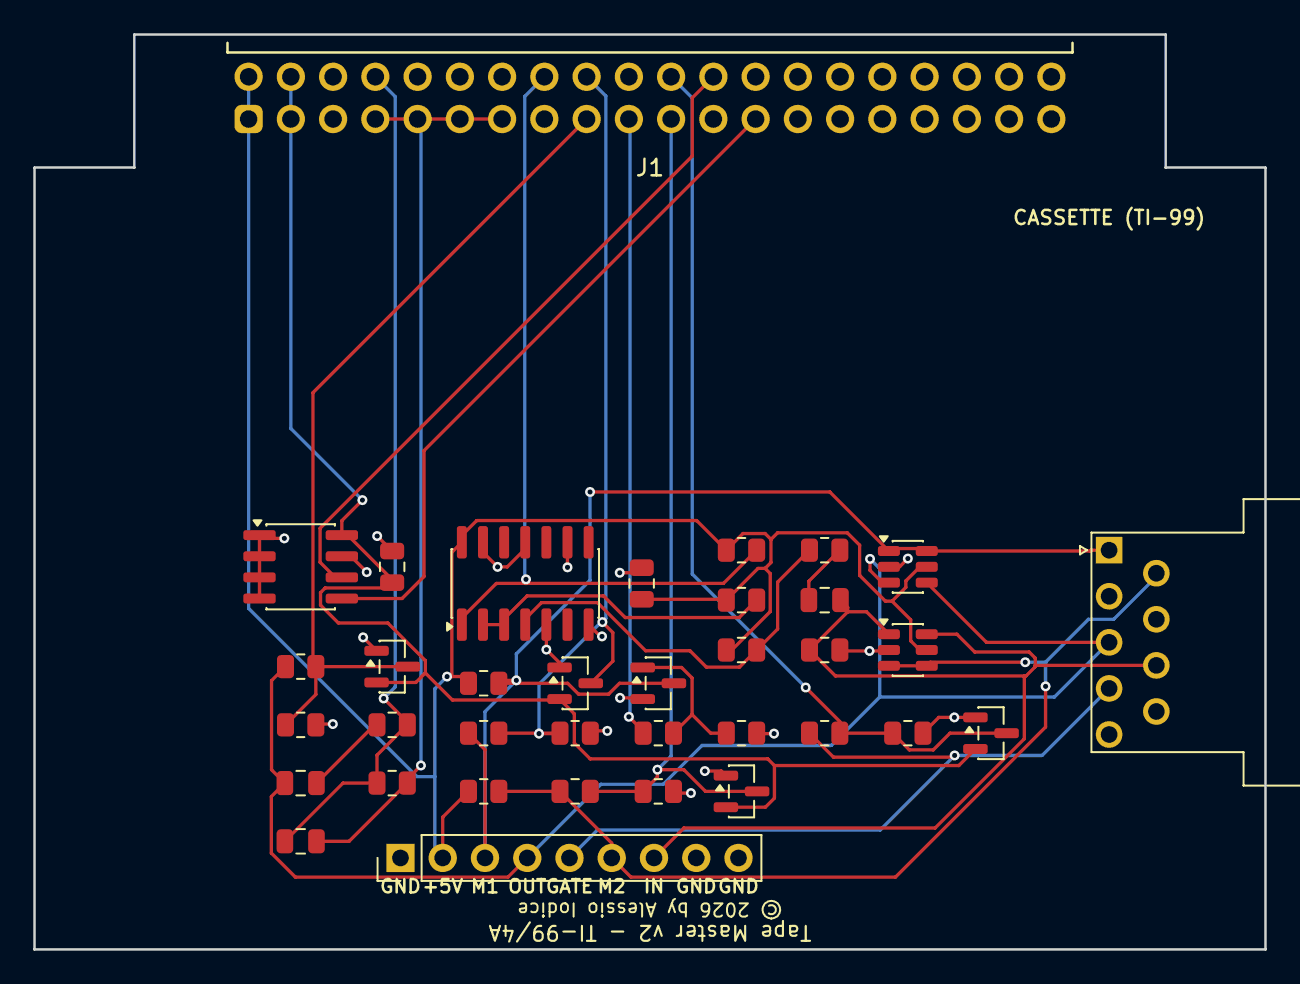
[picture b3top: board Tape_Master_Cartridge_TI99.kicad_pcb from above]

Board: 2 copper layers, 74.0 x 55.0 mm, 36 parts (0 on the bottom side), 23 nets.

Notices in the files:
kicad/v2/Cartridges/01_Commodore_C2N/Tape_Master_Cartridge_C2N.kicad_pcb:
License: CC BY-NC-SA 4.0
